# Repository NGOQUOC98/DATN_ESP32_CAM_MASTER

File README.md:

# DATN_ESP32_CAM_MASTER
## Hardware

### Schematics

### 3D

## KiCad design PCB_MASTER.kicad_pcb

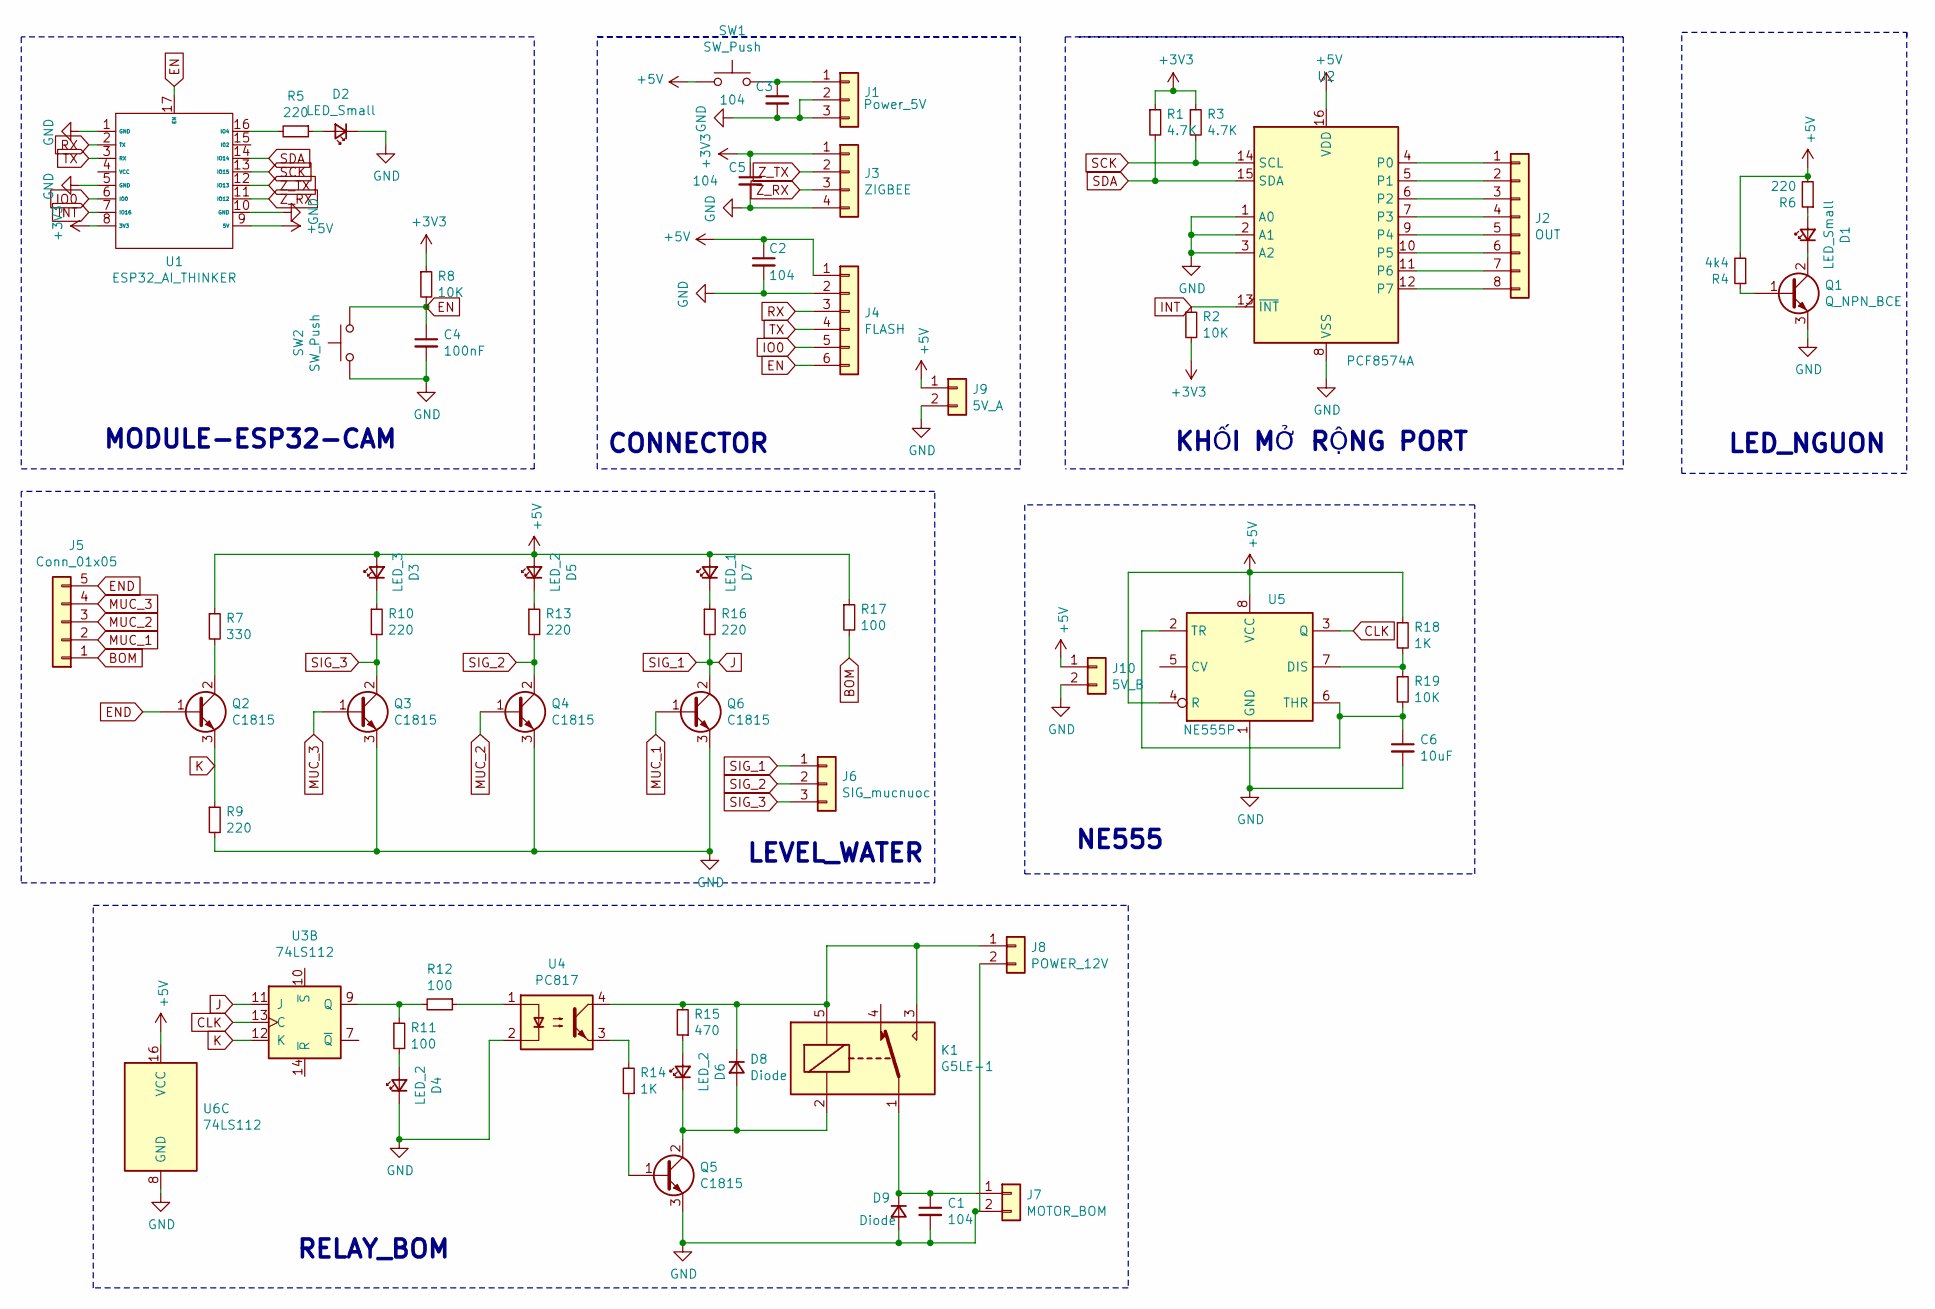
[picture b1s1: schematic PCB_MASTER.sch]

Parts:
C1, C2, C3, C5: 104; CP_Radial_D5.0mm_P2.50mm
C4: 100nF; CP_Radial_D5.0mm_P2.50mm
C6: 10uF; CP_Radial_D5.0mm_P2.50mm
D1, D2: LED_Small; LED_D3.0mm
D3: LED_3; LED_D3.0mm
D4, D5, D6: LED_2; LED_D3.0mm
D7: LED_1; LED_D3.0mm
D8, D9: Diode; PinHeader_1x02_P2.00mm_Vertical
J1: Power_5V; jack_DC
J2: OUT; PinSocket_1x08_P2.54mm_Vertical
J3: ZIGBEE; PinSocket_1x04_P2.54mm_Vertical
J4: FLASH; PinHeader_1x06_P2.54mm_Vertical
J5: Conn_01x05; PinHeader_1x05_P2.54mm_Vertical
J6: SIG_mucnuoc; PinHeader_1x03_P2.54mm_Vertical
J7: MOTOR_BOM; TerminalBlock_bornier-2_P5.08mm
J8: POWER_12V; TerminalBlock_bornier-2_P5.08mm
J9: 5V_A; PinHeader_1x02_P2.54mm_Vertical
J10: 5V_B; PinHeader_1x02_P2.54mm_Vertical
K1: G5LE-1; Relay_SPDT_Omron-G5LE-1
Q1: Q_NPN_BCE; PinSocket_1x03_P1.27mm_Vertical
Q2, Q3, Q4, Q5, Q6: C1815; PinHeader_1x03_P2.00mm_Vertical
R1, R3: 4.7K; R_Box_L13.0mm_W4.0mm_P9.00mm
R2: 10K; R_Axial_DIN0207_L6.3mm_D2.5mm_P15.24mm_Horizontal
R4: 4k4; R_Box_L13.0mm_W4.0mm_P9.00mm
R5, R6, R9, R10, R13, R16: 220; R_Box_L13.0mm_W4.0mm_P9.00mm
R7: 330; R_Box_L13.0mm_W4.0mm_P9.00mm
R8, R19: 10K; R_Box_L13.0mm_W4.0mm_P9.00mm
R11, R12, R17: 100; R_Box_L13.0mm_W4.0mm_P9.00mm
R14, R18: 1K; R_Box_L13.0mm_W4.0mm_P9.00mm
R15: 470; R_Box_L13.0mm_W4.0mm_P9.00mm
SW1, SW2: SW_Push; PinHeader_1x02_P2.54mm_Vertical
U1: ESP32_AI_THINKER; ESP_CAM
U2: PCF8574A; DIP-16_W7.62mm
U3, U6: 74LS112; DIP-16_W7.62mm_LongPads
U4: PC817; DIP-4_W7.62mm
U5: NE555P; DIP-8_W7.62mm

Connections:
+3V3: C5.1, J3.1, R1.1, R2.2, R3.1, R8.1, U1.8 (3V3)
+5V: C2.1, D3.2 (A), D5.2 (A), D7.2 (A), J4.1, J9.1, J10.1, R4.2, R6.2, R7.1, R17.1, R18.1, SW1.1, U1.9 (5V), U2.16 (VDD), U5.4 (R), U5.8 (VCC), U6.16 (VCC)
BOM: J5.1, R17.2
CLK: U3.13 (C), U5.3 (Q)
EN: C4.1, J4.6, R8.2, SW2.2, U1.17 (EN)
END: J5.5, Q2.1 (B)
GND: C1.2, C2.2, C3.2, C4.2, C5.2, C6.2, D2.1 (K), D4.1 (K), D9.2 (A), J1.2, J1.3, J3.4, J4.2, J7.2, J8.2, J9.2, J10.2, Q1.3 (E), Q3.3 (E), Q4.3 (E), Q5.3 (E), Q6.3 (E), R9.2, SW2.1, U1.1 (GND), U1.5 (GND), U1.10 (GND), U2.1 (A0), U2.2 (A1), U2.3 (A2), U2.8 (VSS), U4.2, U5.1 (GND), U6.8 (GND)
INT: R2.1, U1.7 (IO16), U2.13 (~INT~)
IO0: J4.5, U1.6 (IO0)
J: J6.1, Q6.2 (C), R16.2, U3.11 (J)
K: Q2.3 (E), R9.1, U3.12 (K)
MUC_1: J5.2, Q6.1 (B)
MUC_2: J5.3, Q4.1 (B)
MUC_3: J5.4, Q3.1 (B)
unnamed: C1.1, D9.1 (K), J7.1, K1.1
unnamed: C3.1, J1.1, SW1.2
unnamed: C6.1, R19.2, U5.2 (TR), U5.6 (THR)
unnamed: D1.1 (K), Q1.2 (C)
unnamed: D1.2 (A), R6.1
unnamed: D2.2 (A), R5.1
unnamed: D3.1 (K), R10.1
unnamed: D4.2 (A), R11.2
unnamed: D5.1 (K), R13.1
unnamed: D6.1 (K), D8.2 (A), K1.2, Q5.2 (C)
unnamed: D6.2 (A), R15.1
unnamed: D7.1 (K), R16.1
unnamed: D8.1 (K), J8.1, K1.3, K1.5, R15.2, U4.4
unnamed: J2.1, U2.4 (P0)
unnamed: J2.2, U2.5 (P1)
unnamed: J2.3, U2.6 (P2)
unnamed: J2.4, U2.7 (P3)
unnamed: J2.5, U2.9 (P4)
unnamed: J2.6, U2.10 (P5)
unnamed: J2.7, U2.11 (P6)
unnamed: J2.8, U2.12 (P7)
unnamed: Q1.1 (B), R4.1
unnamed: Q2.2 (C), R7.2
unnamed: Q5.1 (B), R14.1
unnamed: R5.2, U1.16 (IO4)
unnamed: R11.1, R12.2, U3.9 (Q)
unnamed: R12.1, U4.1
unnamed: R14.2, U4.3
unnamed: R18.2, R19.1, U5.7 (DIS)
RX: J4.3, U1.2 (TX)
SCK: R3.2, U1.13 (IO15), U2.14 (SCL)
SDA: R1.2, U1.14 (IO14), U2.15 (SDA)
SIG_2: J6.2, Q4.2 (C), R13.2
SIG_3: J6.3, Q3.2 (C), R10.2
TX: J4.4, U1.3 (RX)
Z_RX: J3.3, U1.11 (IO12)
Z_TX: J3.2, U1.12 (IO13)

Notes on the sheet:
MODULE-ESP32-CAM
KHỐI MỞ RỘNG PORT
RELAY_BOM
NE555
LEVEL_WATER
CONNECTOR
LED_NGUON

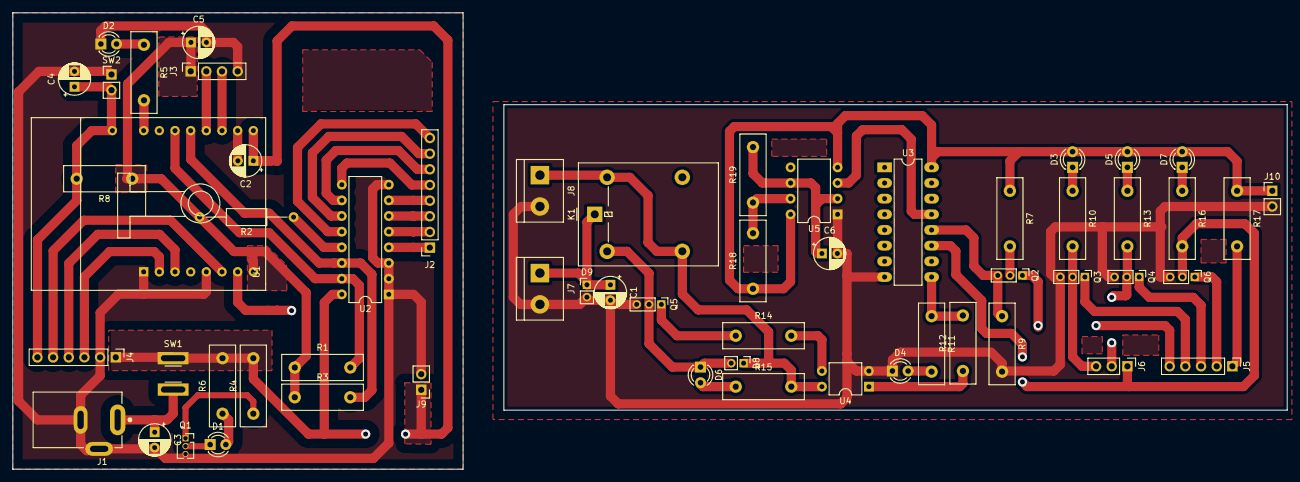
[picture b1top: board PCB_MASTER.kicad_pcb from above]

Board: 2 copper layers, 206.6 x 74.0 mm, 58 parts (0 on the bottom side), 51 nets.

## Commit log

2021-01-09 add file
